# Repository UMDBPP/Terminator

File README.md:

# Terminator
A flight termination device for BPP.

## `T1100` - Current Revision

Much the same as T1000 but simpler and more complete.

## `T1000`
Shipman's ENEE499L project. The digital portion integrates a STM32L4, GPS, P/T Sensor, FRAM, and SX1262 Radio. This should provide quite a bit of flexibility in a small package while consuming minimal power. The digital board interfaces with a cutdown board which performs hot-wire termination like many other designs. However, this board is really just a barebones buck converter power stage that will be controlled by the digital board. This should provide increased flexiblity and efficiency over other implementations while also allowing T1000 to terminate even 550 paracord.

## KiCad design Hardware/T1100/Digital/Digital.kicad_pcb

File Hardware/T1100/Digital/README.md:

View in your browser: https://kicanvas.org/?repo=https%3A%2F%2Fgithub.com%2FUMDBPP%2FTerminator%2Ftree%2Fmain%2FHardware%2FT1100%2FDigital

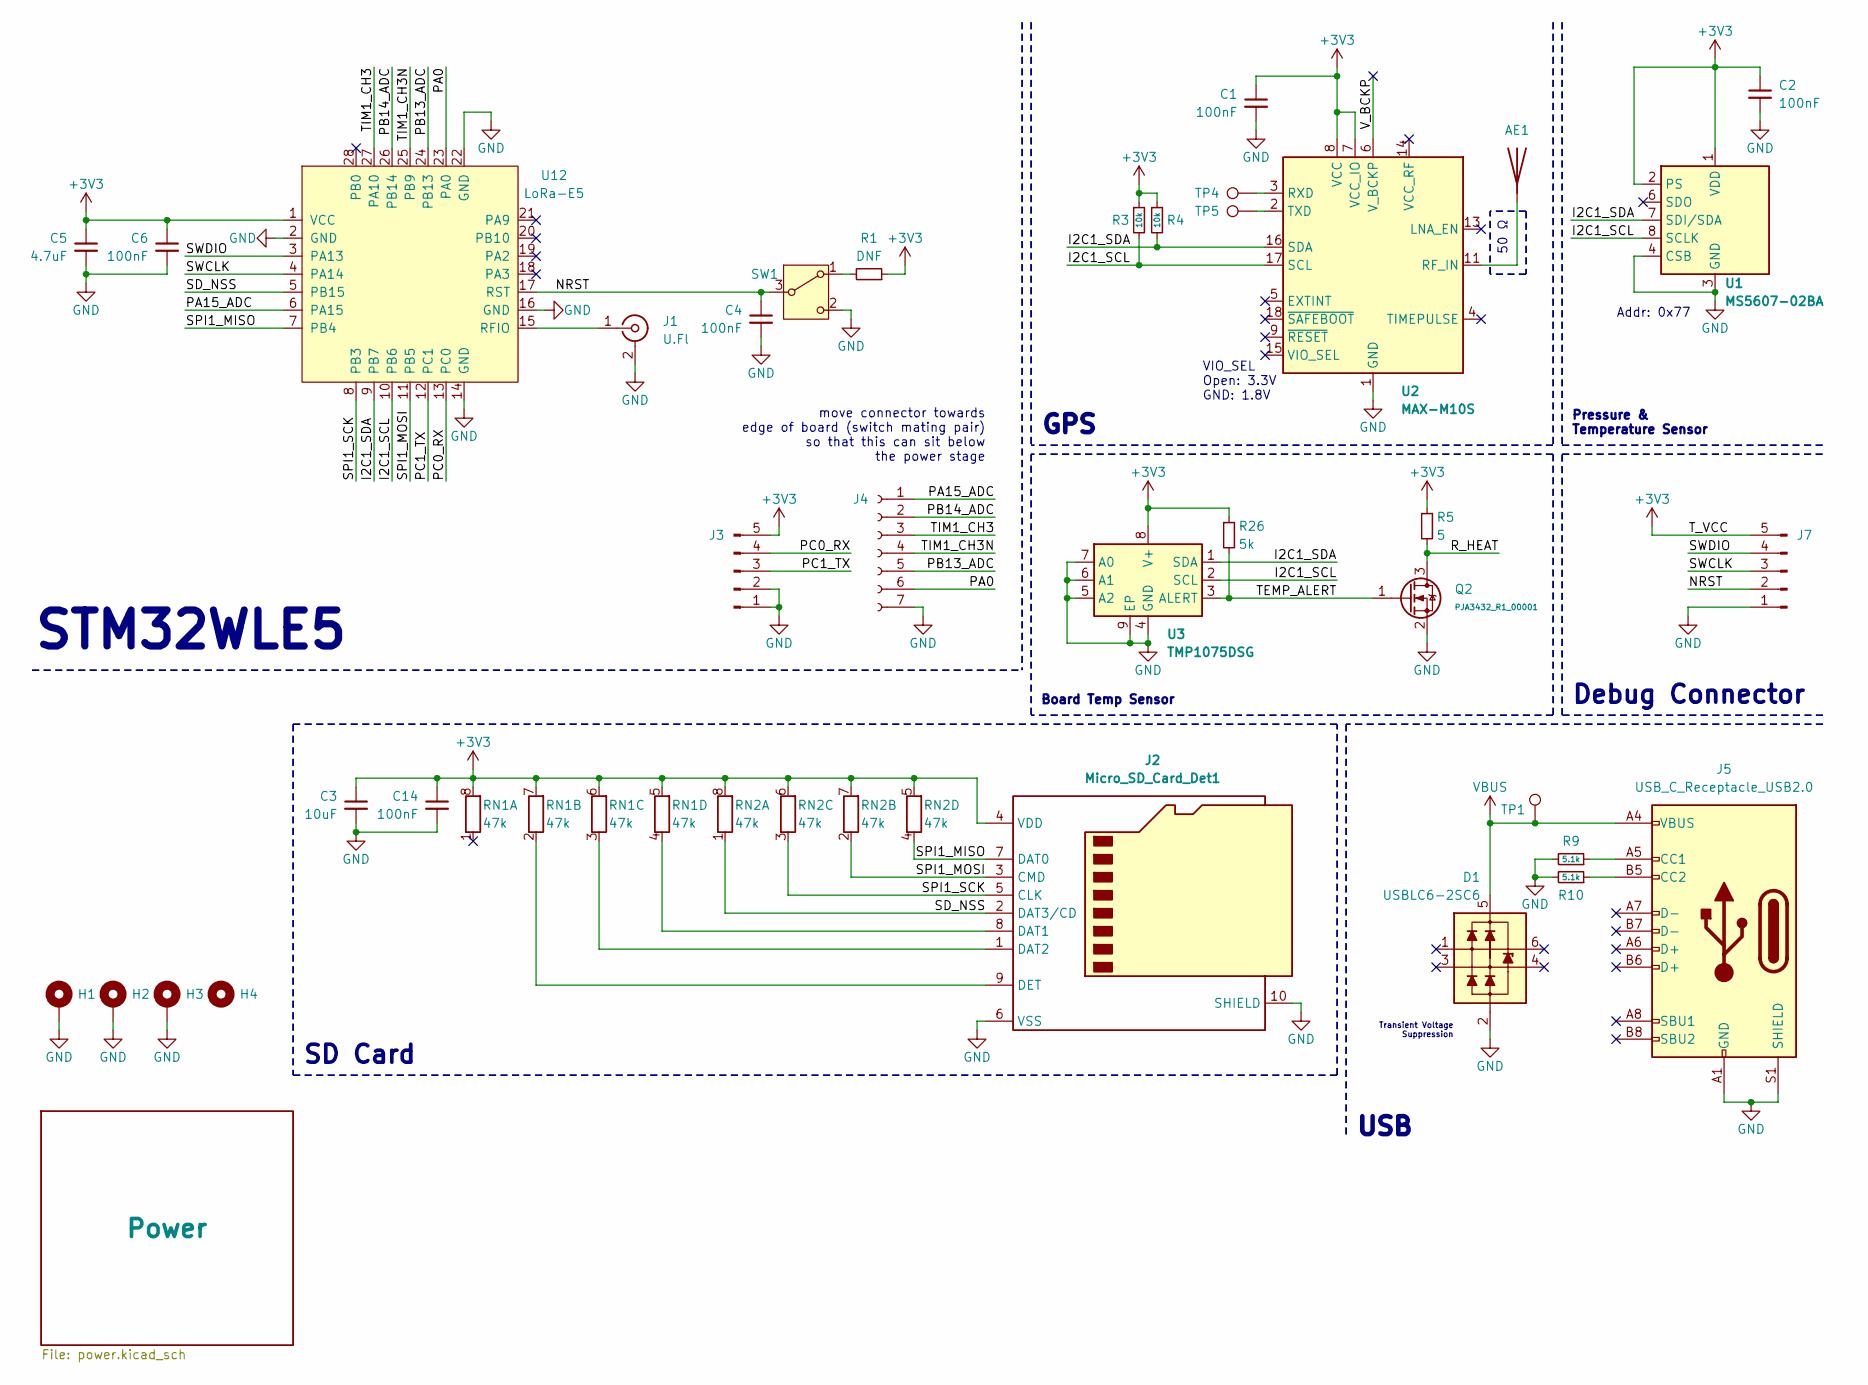
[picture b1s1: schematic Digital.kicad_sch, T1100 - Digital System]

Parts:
AE1: Antenna; ANT_1575AT_JOT-M
C1, C2, C4, C6, C14: 100nF; C_0402_1005Metric
C3: 10uF; C_0603_1608Metric
C5: 4.7uF; C_0603_1608Metric
D1: USBLC6-2SC6; TSOT-23-6
H1, H2, H3: MountingHole_Pad; Mounting_Wuerth_WA-SMSI-M2_H2mm_9774020243
H4: MountingHole; MountingHole_2.2mm_M2_DIN965
J1: U.Fl; U.FL_Molex_MCRF_73412-0110_Vertical
J2: Micro_SD_Card_Det1; microSD_HC_Molex_104031-0811
J3, J7: Conn_01x05_Pin; PinHeader_1x05_P2.54mm_Vertical
J4: Conn_01x07_Socket; Molex_ 1718570007
J5: USB_C_Receptacle_USB2.0; USB_C_Receptacle_GCT_USB4105-xx-A_16P_TopMnt_Horizontal
Q2: PJA3432_R1_00001; SOT-23
R1: DNF; R_0402_1005Metric
R3, R4: 10k; R_0402_1005Metric
R5: 5; R_0603_1608Metric
R9, R10: 5.1k; R_0402_1005Metric
R26: 5k; R_0402_1005Metric
RN1, RN2: 47k; R_Array_Convex_4x1206
SW1: SW_SPDT; CAS-120TB_NDC-M
TP1: TestPoint; TestPoint_Pad_D1.0mm
TP4, TP5: TestPoint; TestPoint_Pad_D3.0mm
U1: MS5607-02BA; LGA-8_3x5mm_P1.25mm
U2: MAX-M10S; ublox_MAX
U3: TMP1075DSG; WSON-8-1EP_2x2mm_P0.5mm_EP0.9x1.6mm_ThermalVias
U12: LoRa-E5

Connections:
+3V3: C1.1, C2.1, C3.1, C5.1, C6.1, C14.1, J2.4 (VDD), J3.5, J7.5, R1.1, R3.1, R4.1, R5.1, R26.1, RN1.5 (R4.2), RN1.6 (R3.2), RN1.7 (R2.2), RN1.8 (R1.2), RN2.5 (R4.2), RN2.6 (R3.2), RN2.7 (R2.2), RN2.8 (R1.2), U1.1 (VDD), U1.2 (PS), U2.7 (VCC_IO), U2.8 (VCC), U3.8 (V+), U12.1 (VCC); also elsewhere on the board
/I2C1_SCL: R3.2, U1.8 (SCLK), U2.17 (SCL), U3.2 (SCL), U12.10 (PB6)
/I2C1_SDA: R4.2, U1.7 (SDI/SDA), U2.16 (SDA), U3.1 (SDA), U12.9 (PB7)
/NRST: C4.1, J7.2, SW1.3 (C), U12.17 (RST)
/PA0: J4.6, U12.23 (PA0)
/PA15_ADC: J4.1, U12.6 (PA15)
/PB13_ADC: J4.5, U12.24 (PB13~)
/PB14_ADC: J4.2, U12.26 (PB14)
/PC0_RX: J3.4, U12.13 (PC0)
/PC1_TX: J3.3, U12.12 (PC1)
/R_HEAT: Q2.3 (D), R5.2
/SD_NSS: J2.2 (DAT3/CD), RN2.1 (R1.1), U12.5 (PB15)
/SPI1_MISO: J2.7 (DAT0), RN2.4 (R4.1), U12.7 (PB4)
/SPI1_MOSI: J2.3 (CMD), RN2.2 (R2.1), U12.11 (PB5)
/SPI1_SCK: J2.5 (CLK), RN2.3 (R3.1), U12.8 (PB3)
/SWCLK: J7.3, U12.4 (PA14)
/SWDIO: J7.4, U12.3 (PA13)
/TEMP_ALERT: Q2.1 (G), R26.2, U3.3 (ALERT)
/TIM1_CH3: J4.3, U12.27 (PA10)
/TIM1_CH3N: J4.4, U12.25 (PB9)
/V_BCKP: U2.6 (V_BCKP)
GND: C1.2, C2.2, C3.2, C4.2, C5.2, C6.2, C14.2, D1.2 (VN), H1.1, H2.1, H3.1, J1.2 (Ext), J2.6 (VSS), J2.10 (SHIELD), J3.1, J3.2, J4.7, J5.A1 (GND), J5.A12 (GND), J5.B1 (GND), J5.B12 (GND), J5.S1 (SHIELD), J7.1, Q2.2 (S), R9.2, R10.2, SW1.2 (B), U1.3 (GND), U1.4 (CSB), U1.5 (CSB), U2.1 (GND), U2.10 (GND), U2.12 (GND), U3.4 (GND), U3.5 (A2), U3.6 (A1), U3.7 (A0), U3.9 (EP), U12.2 (GND), U12.14 (GND), U12.16 (GND), U12.22 (GND); also elsewhere on the board
unnamed: AE1.1 (A), U2.11 (RF_IN)
unnamed: J1.1 (In), U12.15 (RFIO)
unnamed: J2.8 (DAT1), RN1.4 (R4.1)
unnamed: J2.1 (DAT2), RN1.3 (R3.1)
unnamed: J2.9 (DET), RN1.2 (R2.1)
unnamed: J5.A5 (CC1), R9.1
unnamed: J5.B5 (CC2), R10.1
unnamed: R1.2, SW1.1 (A)
unnamed: TP4.1, U2.3 (RXD)
unnamed: TP5.1, U2.2 (TXD)
VBUS: D1.5 (VP), J5.A4 (VBUS), J5.A9 (VBUS), J5.B4 (VBUS), J5.B9 (VBUS), TP1.1; also elsewhere on the board

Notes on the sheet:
GPS
Transient Voltage Suppression
Board Temp Sensor
VIO_SEL Open: 3.3V GND: 1.8V
Debug Connector
SD Card
50 Ω
USB
Pressure & Temperature Sensor
move connector towards edge of board (switch mating pair) so that this can sit below the power stage
STM32WLE5
Addr: 0x77

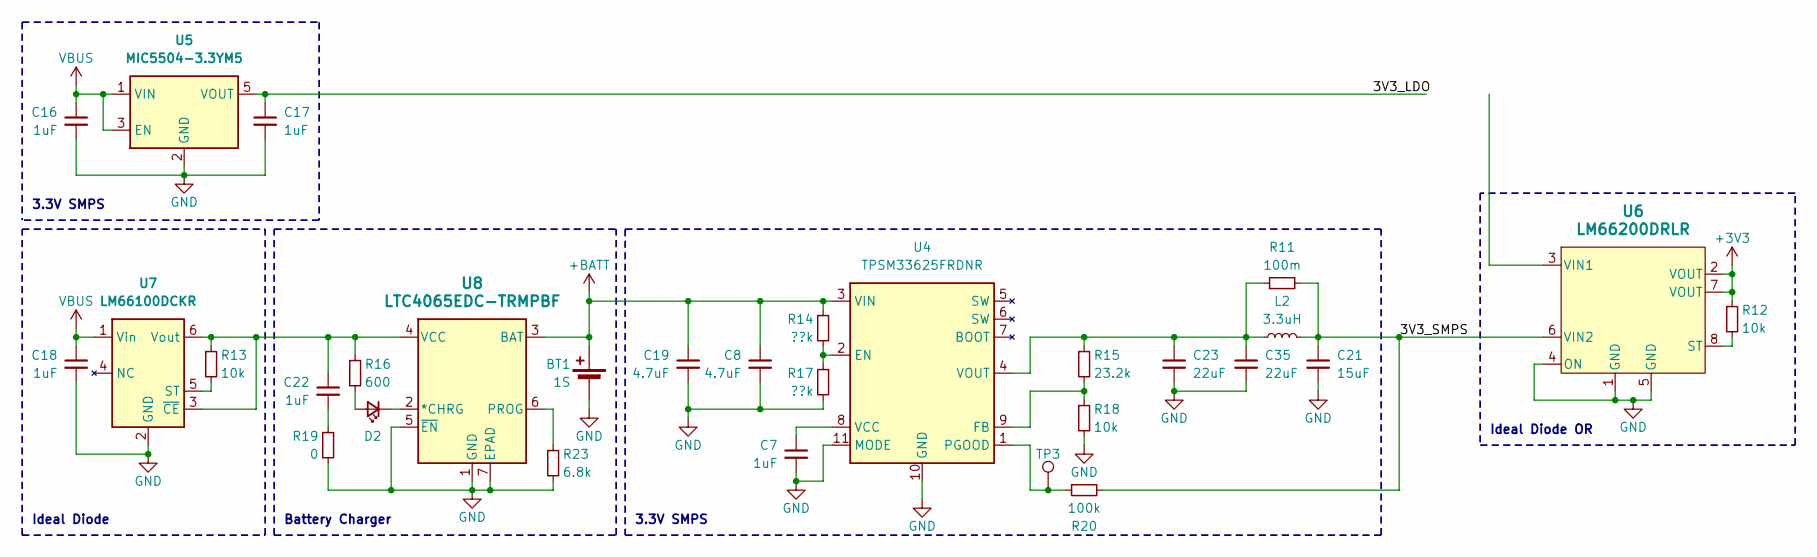
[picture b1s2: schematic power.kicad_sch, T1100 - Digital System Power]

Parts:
BT1: 1S; PinHeader_1x02_P2.54mm_Vertical
C7: 1uF; C_0402_1005Metric
C8, C19: 4.7uF; C_0805_2012Metric
C16, C17, C18, C22: 1uF; C_0603_1608Metric
C21: 15uF; C_1206_3216Metric
C23, C35: 22uF; C_0805_2012Metric
D2: LED_Small; LED_0603_1608Metric
L2: 3.3uH; L_1210_3225Metric
R11: 100m; R_0402_1005Metric
R12, R13, R18: 10k; R_0402_1005Metric
R14, R17: ??k; R_0402_1005Metric
R15: 23.2k; R_0402_1005Metric
R16: 600; R_0402_1005Metric
R19: 0; R_0402_1005Metric
R20: 100k; R_0402_1005Metric
R23: 6.8k; R_0402_1005Metric
TP3: TestPoint; TestPoint_Pad_D1.0mm
U4: TPSM33625FRDNR; RDN0011A-MFG-NO-VIA
U5: MIC5504-3.3YM5; SOT-23-5
U6: LM66200DRLR; SOT-5X3_DRL_TEX
U7: LM66100DCKR; SOT-363_SC-70-6
U8: LTC4065EDC-TRMPBF; DFN-6_DC_LIT

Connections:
+3V3: R12.1, U6.2 (VOUT), U6.7 (VOUT); also elsewhere on the board
+BATT: BT1.1 (+), C8.1, C19.1, R14.1, U4.3 (VIN), U8.3 (BAT)
/Power/3V3_LDO: C17.1, U5.5 (VOUT)
/Power/3V3_SMPS: C21.1, L2.2, R11.2, R20.2, U6.6 (VIN2)
GND: BT1.2 (-), C7.2, C8.2, C16.2, C17.2, C18.2, C19.2, C21.2, C23.2, C35.2, R17.2, R18.2, R19.2, R23.2, U4.10 (GND), U4.11 (MODE), U5.2 (GND), U6.1 (GND), U6.4 (ON), U6.5 (GND), U7.2 (GND), U8.1 (GND), U8.5 (~EN), U8.7 (EPAD); also elsewhere on the board
unnamed: C22.2, R19.1
unnamed: D2.2 (A), R16.2
unnamed: D2.1 (K), U8.2 (*CHRG)
unnamed: R14.2, R17.1, U4.2 (EN)
unnamed: R15.2, R18.1, U4.9 (FB)
unnamed: R20.1, TP3.1, U4.1 (PGOOD)
unnamed: C7.1, U4.8 (VCC)
unnamed: C23.1, C35.1, L2.1, R11.1, R15.1, U4.4 (VOUT)
unnamed: R12.2, U6.8 (ST)
unnamed: R13.2, U7.5 (ST)
unnamed: C22.1, R13.1, R16.1, U7.3 (~CE), U7.6 (Vout), U8.4 (VCC)
unnamed: R23.1, U8.6 (PROG)
VBUS: C16.1, C18.1, U5.1 (VIN), U5.3 (EN), U7.1 (Vin); also elsewhere on the board

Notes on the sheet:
Ideal Diode
Battery Charger
Ideal Diode OR
3.3V SMPS

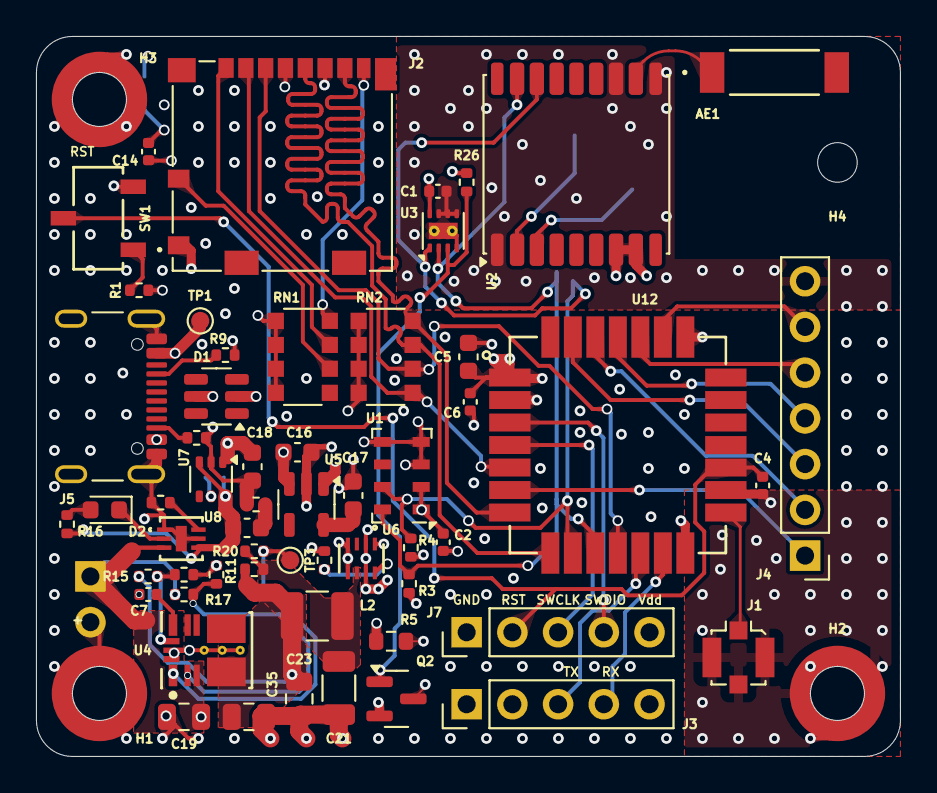
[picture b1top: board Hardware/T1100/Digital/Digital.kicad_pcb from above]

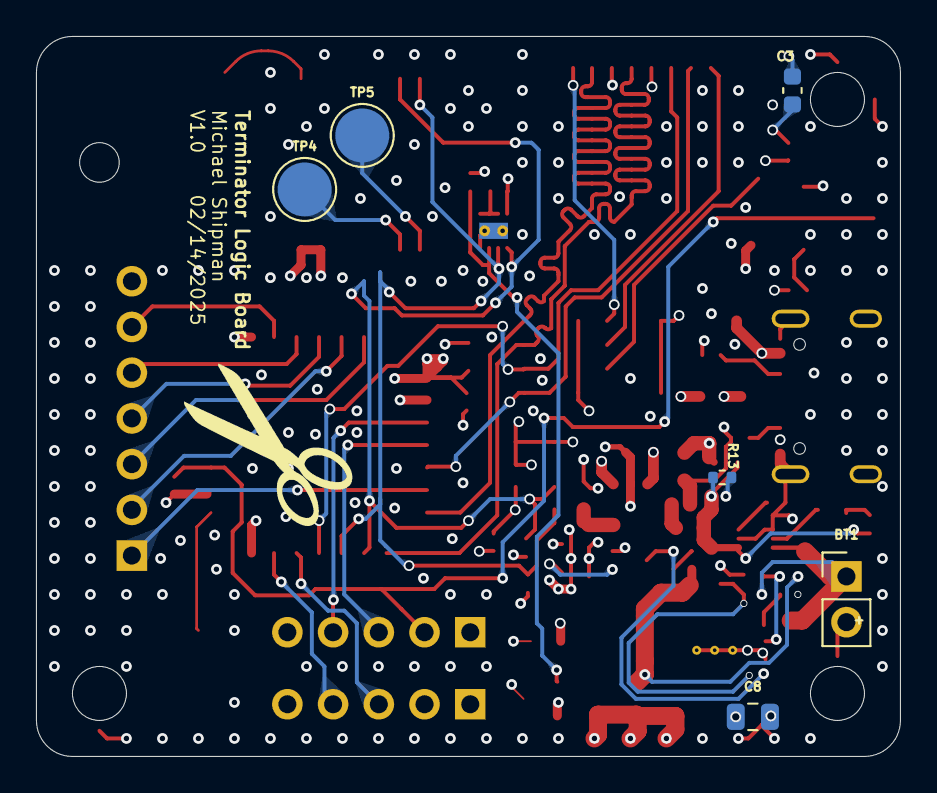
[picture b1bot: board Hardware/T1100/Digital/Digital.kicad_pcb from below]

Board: 6 copper layers, 48.0 x 40.0 mm, 67 parts (6 on the bottom side), 47 nets.

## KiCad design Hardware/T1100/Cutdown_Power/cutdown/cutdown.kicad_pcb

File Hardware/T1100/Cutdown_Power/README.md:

Cutdown power stage for T1000 nichrome. [Click here to view in browser.](https://kicanvas.org/?repo=https%3A%2F%2Fgithub.com%2FUMDBPP%2FTerminator%2Ftree%2Fmain%2FHardware%2FT1100%2FCutdown_Power%2Fcutdown)

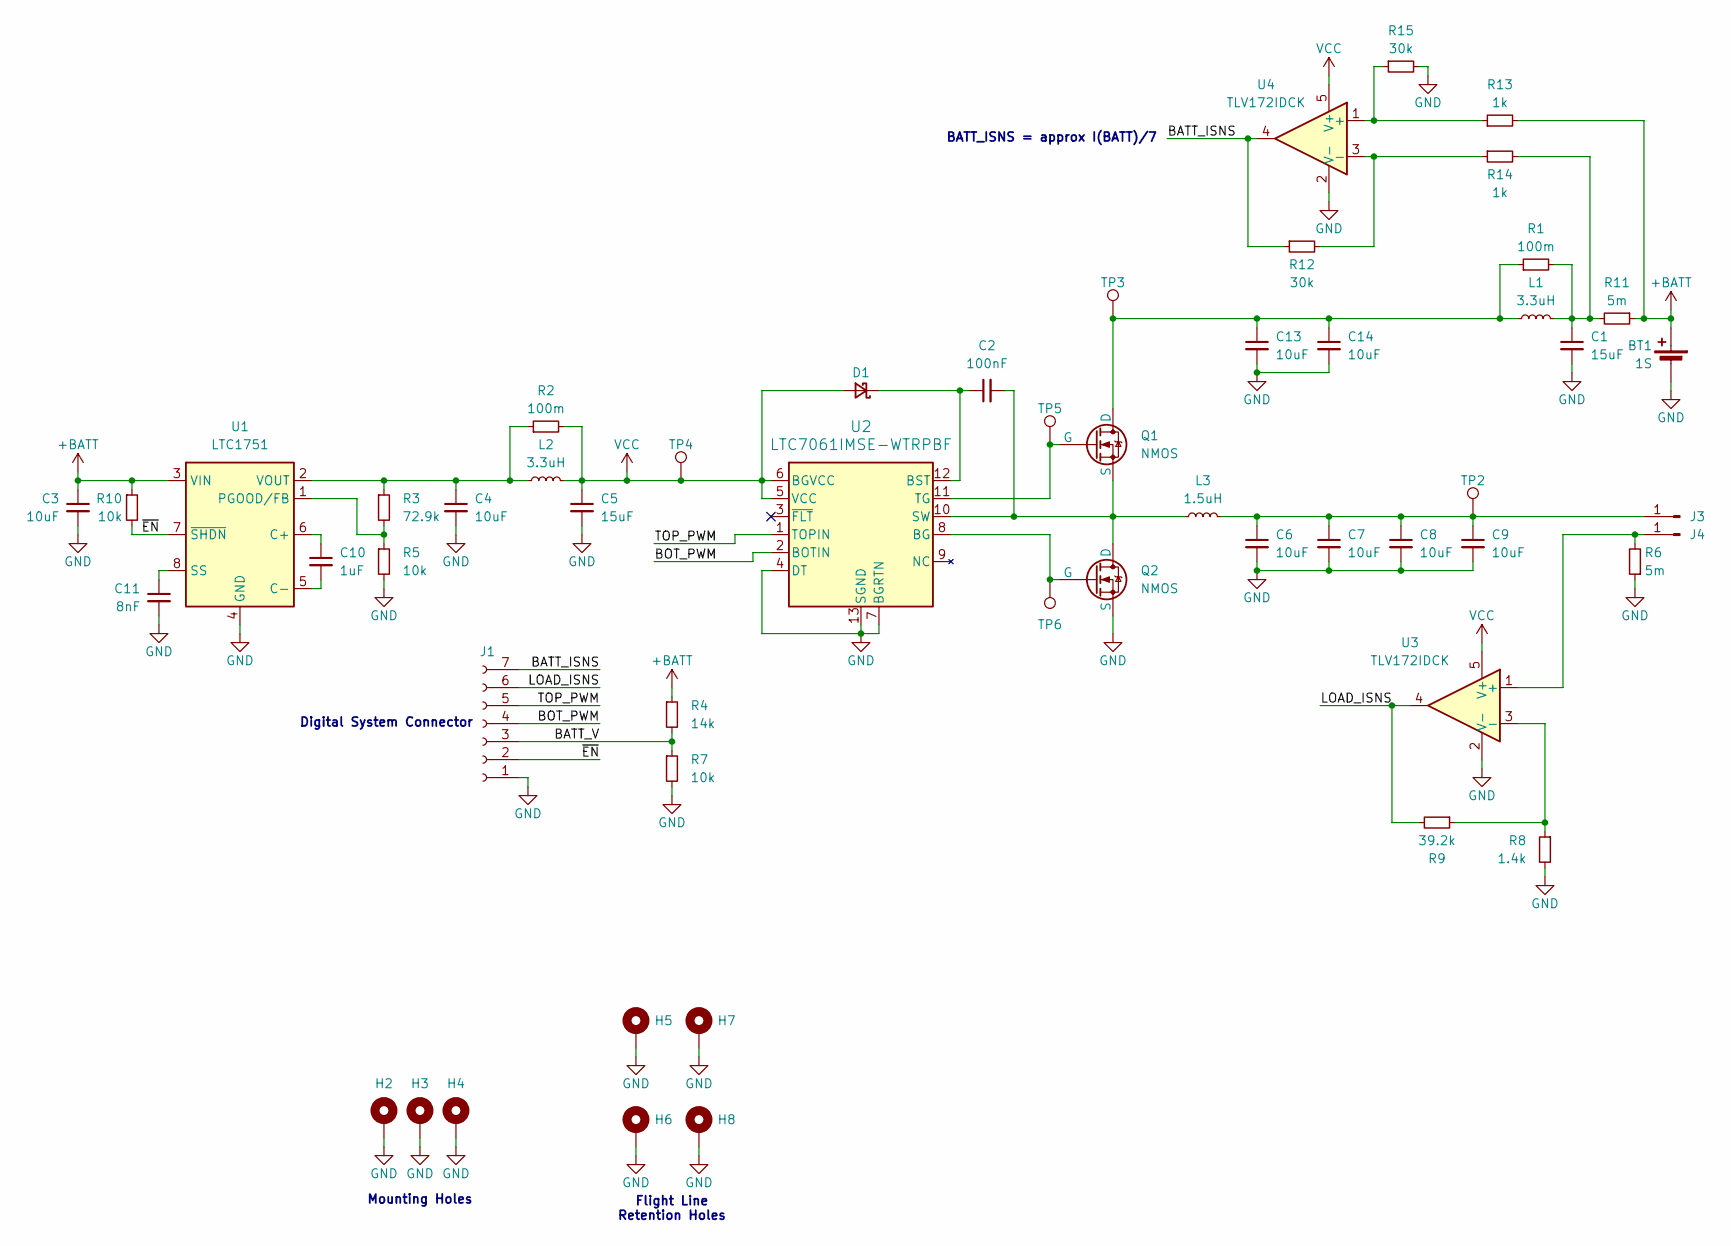
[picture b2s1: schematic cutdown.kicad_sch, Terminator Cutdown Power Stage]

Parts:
BT1: 1S; AMASS_XT30U-F_1x02_P5.0mm_Vertical
C1, C5: 15uF; C_1206_3216Metric
C2: 100nF; C_0603_1608Metric
C3, C4: 10uF; C_0805_2012Metric
C6, C7, C8, C9, C13, C14: 10uF; C_1206_3216Metric
C10: 1uF; C_0603_1608Metric
C11: 8nF; C_0603_1608Metric
D1: D_Schottky_Small; D_SOD-123F
H2, H3, H4: MountingHole_Pad; MountingHole_2.2mm_M2_DIN965_Pad
H5, H6, H7, H8: MountingHole_Pad; Mounting_Wuerth_WA-SMSI-M2_H2mm_9774020243
J1: Conn_01x07_Socket; Molex_ 1718570007
J3, J4: Conn_01x01_Pin; Mounting_Wuerth_WA-SMSI-M2_H2mm_9774020243
L1, L2: 3.3uH; L_1210_3225Metric
L3: 1.5uH; IHLP2020CZER1R5M8A
Q1, Q2: NMOS; CSD17307Q5A
R1, R2: 100m; C_0603_1608Metric
R3: 72.9k; R_0402_1005Metric
R4: 14k; R_0402_1005Metric
R5, R7, R10: 10k; R_0402_1005Metric
R6, R11: 5m; R_2512_6332Metric
R8: 1.4k; R_0603_1608Metric_Pad0.98x0.95mm_HandSolder
R9: 39.2k; R_0603_1608Metric_Pad0.98x0.95mm_HandSolder
R12, R15: 30k; R_0402_1005Metric
R13, R14: 1k; R_0402_1005Metric
TP2, TP3, TP4: TestPoint; TestPoint_Keystone_5000-5004_Miniature
TP5, TP6: TestPoint; TestPoint_Pad_D1.0mm
U1: LTC1751; MSOP-8_3x3mm_P0.65mm
U2: LTC7061IMSE-WTRPBF; MSOP-12-1EP_3x4mm_P0.65mm_EP1.65x2.85mm
U3, U4: TLV172IDCK; SOT-353_SC-70-5

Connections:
+BATT: BT1.2 (+), C3.1, R4.1, R10.1, R11.1, R13.2, U1.3 (VIN)
/BATT_ISNS: J1.7, R12.1, U4.4
/BATT_V: J1.3, R4.2, R7.1
/BOT_PWM: J1.4, U2.2 (BOTIN)
/LOAD_ISNS: J1.6, R9.2, U3.4
/TOP_PWM: J1.5, U2.1 (TOPIN)
/~EN: J1.2, R10.2, U1.7 (~SHDN)
GND: BT1.1 (-), C1.2, C3.2, C4.2, C5.2, C6.2, C7.2, C8.2, C9.2, C11.2, C13.2, C14.2, H2.1, H3.1, H4.1, H5.1, H6.1, H7.1, H8.1, J1.1, Q2.3 (S), R5.2, R6.1, R7.2, R8.2, R15.2, U1.4 (GND), U2.4 (DT), U2.7 (BGRTN), U2.13 (SGND), U3.2 (V-), U4.2 (V-)
unnamed: C1.1, L1.2, R1.2, R11.2, R14.2
unnamed: C2.1, D1.1 (K), U2.12 (BST)
unnamed: C6.1, C7.1, C8.1, C9.1, J3.1, L3.2, TP2.1
unnamed: J4.1, R6.2, U3.1 (+)
unnamed: C13.1, C14.1, L1.1, Q1.1 (D), R1.1, TP3.1
unnamed: Q1.2 (G), TP5.1, U2.11 (TG)
unnamed: C2.2, L3.1, Q1.3 (S), Q2.1 (D), U2.10 (SW)
unnamed: Q2.2 (G), TP6.1, U2.8 (BG)
unnamed: C10.1, U1.6 (C+)
unnamed: C10.2, U1.5 (C-)
unnamed: R3.2, R5.1, U1.1 (PGOOD/FB)
unnamed: C11.1, U1.8 (SS)
unnamed: C4.1, L2.1, R2.1, R3.1, U1.2 (VOUT)
unnamed: R8.1, R9.1, U3.3 (-)
unnamed: R13.1, R15.1, U4.1 (+)
unnamed: R12.2, R14.1, U4.3 (-)
VCC: C5.1, D1.2 (A), L2.2, R2.2, TP4.1, U2.5 (VCC), U2.6 (BGVCC), U3.5 (V+), U4.5 (V+)

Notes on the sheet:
Digital System Connector
BATT_ISNS = approx I(BATT)/7
Flight Line Retention Holes
Mounting Holes

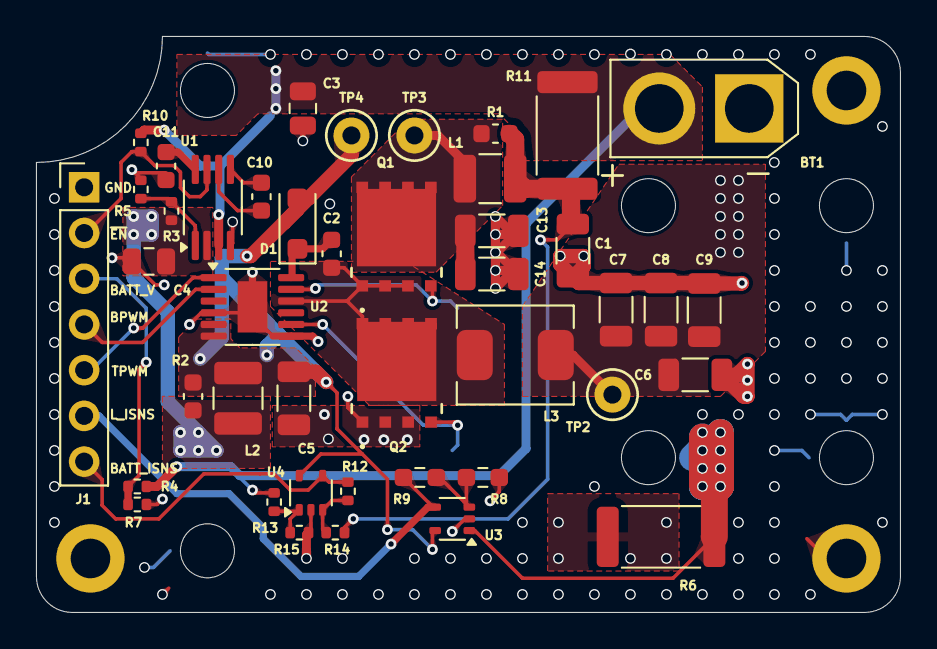
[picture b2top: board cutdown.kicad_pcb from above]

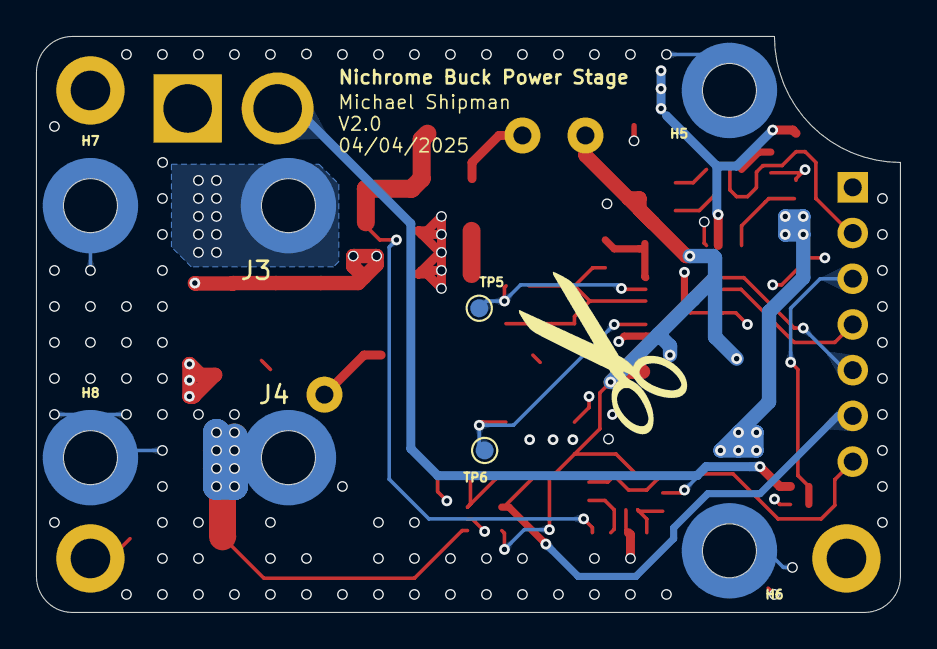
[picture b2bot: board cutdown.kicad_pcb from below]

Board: 4 copper layers, 48.0 x 32.0 mm, 54 parts (8 on the bottom side), 25 nets.

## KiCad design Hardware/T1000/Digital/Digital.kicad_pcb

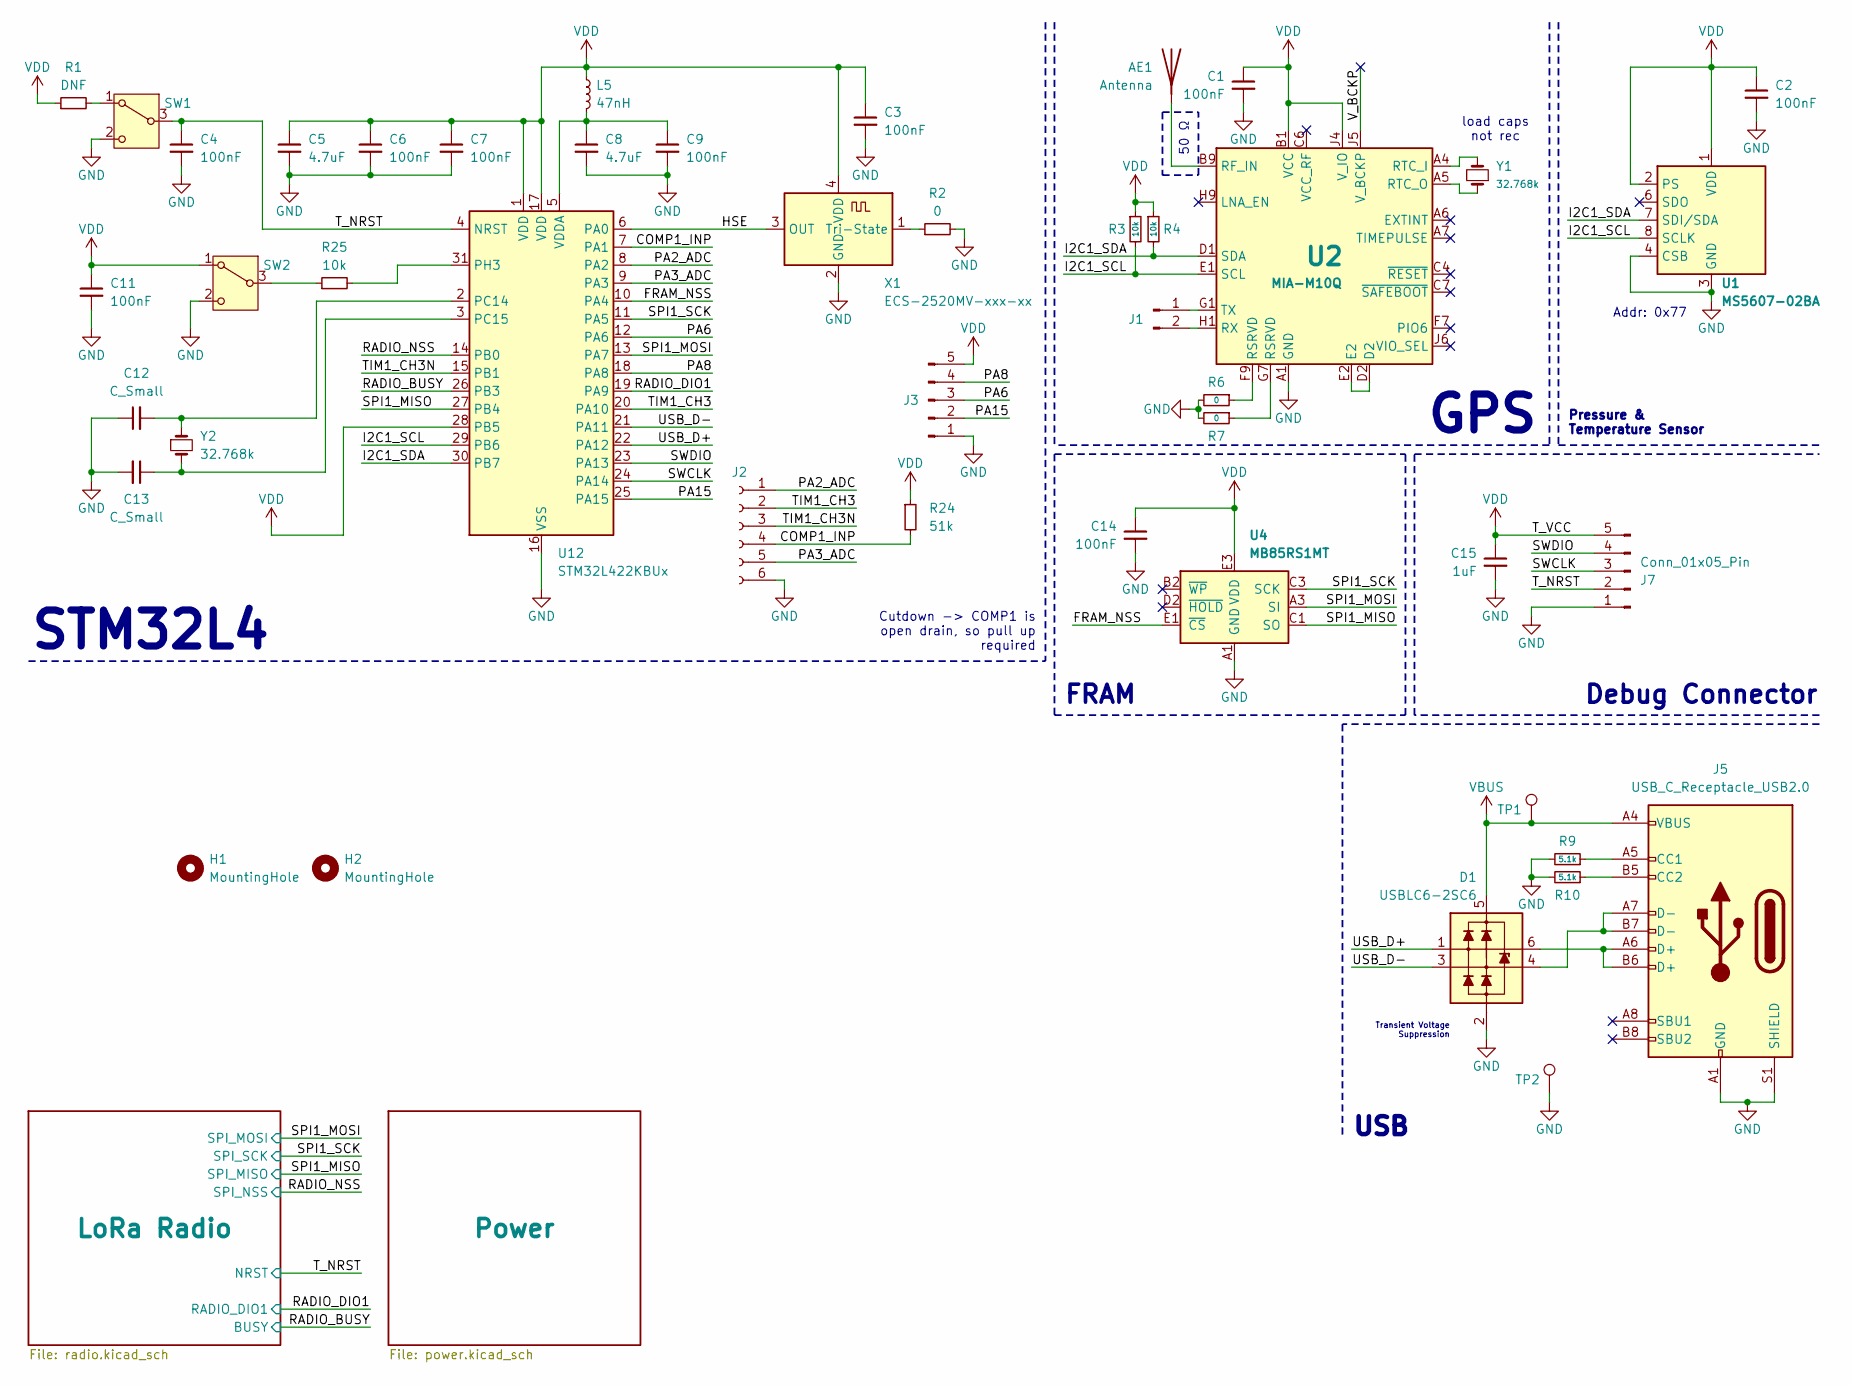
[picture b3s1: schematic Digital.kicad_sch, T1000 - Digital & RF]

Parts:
AE1: Antenna; ANT_1575AT_JOT-M
C1, C2, C3, C4, C6, C7, C9, C11, C14: 100nF; C_0402_1005Metric
C5, C8: 4.7uF; C_0603_1608Metric
C12, C13: C_Small; C_0402_1005Metric
C15: 1uF; C_0603_1608Metric
D1: USBLC6-2SC6; TSOT-23-6
H1, H2: MountingHole; MountingHole_2.2mm_M2
J1: Conn_01x02_Pin; PinHeader_1x02_P2.54mm_Vertical
J2: Conn_01x06_Socket; PinHeader_1x06_P2.54mm_Vertical
J3, J7: Conn_01x05_Pin; PinHeader_1x05_P2.54mm_Vertical
J5: USB_C_Receptacle_USB2.0; USB_C_Receptacle_GCT_USB4105-xx-A_16P_TopMnt_Horizontal
L5: 47nH; L_0402_1005Metric
R1: DNF; R_0402_1005Metric
R2, R6, R7: 0; R_0402_1005Metric
R3, R4, R25: 10k; R_0402_1005Metric
R9, R10: 5.1k; R_0402_1005Metric
R24: 51k; R_0402_1005Metric
SW1, SW2: SW_SPDT; CAS-120TB_NDC-M
TP1, TP2: TestPoint; TestPoint_Pad_D1.0mm
U1: MS5607-02BA; LGA-8_3x5mm_P1.25mm
U2: MIA-M10Q
U4: MB85RS1MT; BGA8CP30X40_5X3_309X228X35B25N
U12: STM32L422KBUx; QFN-32-1EP_5x5mm_P0.5mm_EP3.45x3.45mm
X1: ECS-2520MV-xxx-xx; Oscillator_SMD_ECS_2520MV-xxx-xx-4Pin_2.5x2.0mm
Y1, Y2: 32.768k; Crystal_SMD_3215-2Pin_3.2x1.5mm

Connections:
/COMP1_INP: J2.4, R24.2, U12.7 (PA1)
/FRAM_NSS: U4.E1 (~CS), U12.10 (PA4)
/HSE: U12.6 (PA0), X1.3 (OUT)
/I2C1_SCL: R3.2, U1.8 (SCLK), U2.E1 (SCL), U12.29 (PB6)
/I2C1_SDA: R4.2, U1.7 (SDI/SDA), U2.D1 (SDA), U12.30 (PB7)
/PA2_ADC: J2.1, U12.8 (PA2)
/PA3_ADC: J2.5, U12.9 (PA3)
/PA6: J3.3, U12.12 (PA6)
/PA8: J3.4, U12.18 (PA8)
/PA15: J3.2, U12.25 (PA15)
/RADIO_BUSY: U12.26 (PB3); also elsewhere on the board
/RADIO_DIO1: U12.19 (PA9); also elsewhere on the board
/RADIO_NSS: U12.14 (PB0); also elsewhere on the board
/SPI1_MISO: U4.C1 (SO), U12.27 (PB4); also elsewhere on the board
/SPI1_MOSI: U4.A3 (SI), U12.13 (PA7); also elsewhere on the board
/SPI1_SCK: U4.C3 (SCK), U12.11 (PA5); also elsewhere on the board
/SWCLK: J7.3, U12.24 (PA14)
/SWDIO: J7.4, U12.23 (PA13)
/TIM1_CH3: J2.2, U12.20 (PA10)
/TIM1_CH3N: J2.3, U12.15 (PB1)
/T_NRST: C4.1, J7.2, SW1.3 (C), U12.4 (NRST); also elsewhere on the board
/USB_D+: D1.1 (L1), U12.22 (PA12)
/USB_D-: D1.3 (L2), U12.21 (PA11)
/V_BCKP: U2.J5 (V_BCKP)
GND: C1.2, C2.2, C3.2, C4.2, C5.2, C6.2, C7.2, C8.2, C9.2, C11.2, C12.1, C13.2, C14.2, C15.2, D1.2 (VN), J2.6, J3.1, J5.A1 (GND), J5.A12 (GND), J5.B1 (GND), J5.B12 (GND), J5.S1 (SHIELD), J7.1, R2.2, R6.2, R7.2, R9.2, R10.2, SW1.2 (B), SW2.2 (B), TP2.1, U1.3 (GND), U1.4 (CSB), U1.5 (CSB), U2.A1 (GND), U2.A2 (GND), U2.A3 (GND), U2.A8 (GND), U2.A9 (GND), U2.B2 (GND), U2.B8 (GND), U2.C3 (GND), U2.C9 (GND), U2.E3 (GND), U2.E4 (GND), U2.E9 (GND), U2.F1 (GND), U2.F3 (GND), U2.F4 (GND), U2.G3 (GND), U2.G4 (GND), U2.G5 (GND), U2.G6 (GND), U2.H8 (GND), U2.J8 (GND), U2.J9 (GND), U4.A1 (GND), U12.16 (VSS), U12.32 (VSS), U12.33 (VSS), X1.2 (GND); also elsewhere on the board
unnamed: AE1.1 (A), U2.B9 (RF_IN)
unnamed: D1.6 (L1), J5.A6 (D+), J5.B6 (D+)
unnamed: D1.4 (L2), J5.A7 (D-), J5.B7 (D-)
unnamed: J1.1, U2.G1 (TX)
unnamed: J1.2, U2.H1 (RX)
unnamed: J5.A5 (CC1), R9.1
unnamed: J5.B5 (CC2), R10.1
unnamed: R6.1, U2.F9 (RSRVD)
unnamed: R7.1, U2.G7 (RSRVD)
unnamed: R1.2, SW1.1 (A)
unnamed: R25.1, SW2.3 (C)
unnamed: U2.A4 (RTC_I), Y1.2
unnamed: U2.A5 (RTC_O), Y1.1
unnamed: C12.2, U12.2 (PC14), Y2.1
unnamed: C13.1, U12.3 (PC15), Y2.2
unnamed: R25.2, U12.31 (PH3)
unnamed: C8.1, C9.1, L5.2, U12.5 (VDDA)
unnamed: R2.1, X1.1 (Tri-State)
VBUS: D1.5 (VP), J5.A4 (VBUS), J5.A9 (VBUS), J5.B4 (VBUS), J5.B9 (VBUS), TP1.1; also elsewhere on the board
VDD: C1.1, C2.1, C3.1, C5.1, C6.1, C7.1, C11.1, C14.1, C15.1, J3.5, J7.5, L5.1, R1.1, R3.1, R4.1, R24.1, SW2.1 (A), U1.1 (VDD), U1.2 (PS), U2.B1 (VCC), U2.J4 (V_IO), U4.E3 (VDD), U12.1 (VDD), U12.17 (VDD), U12.28 (PB5), X1.4 (VDD); also elsewhere on the board

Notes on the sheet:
load caps not rec
GPS
Transient Voltage Suppression
Debug Connector
Cutdown -> COMP1 is open drain, so pull up required
FRAM
50 Ω
USB
Pressure & Temperature Sensor
STM32L4
Addr: 0x77

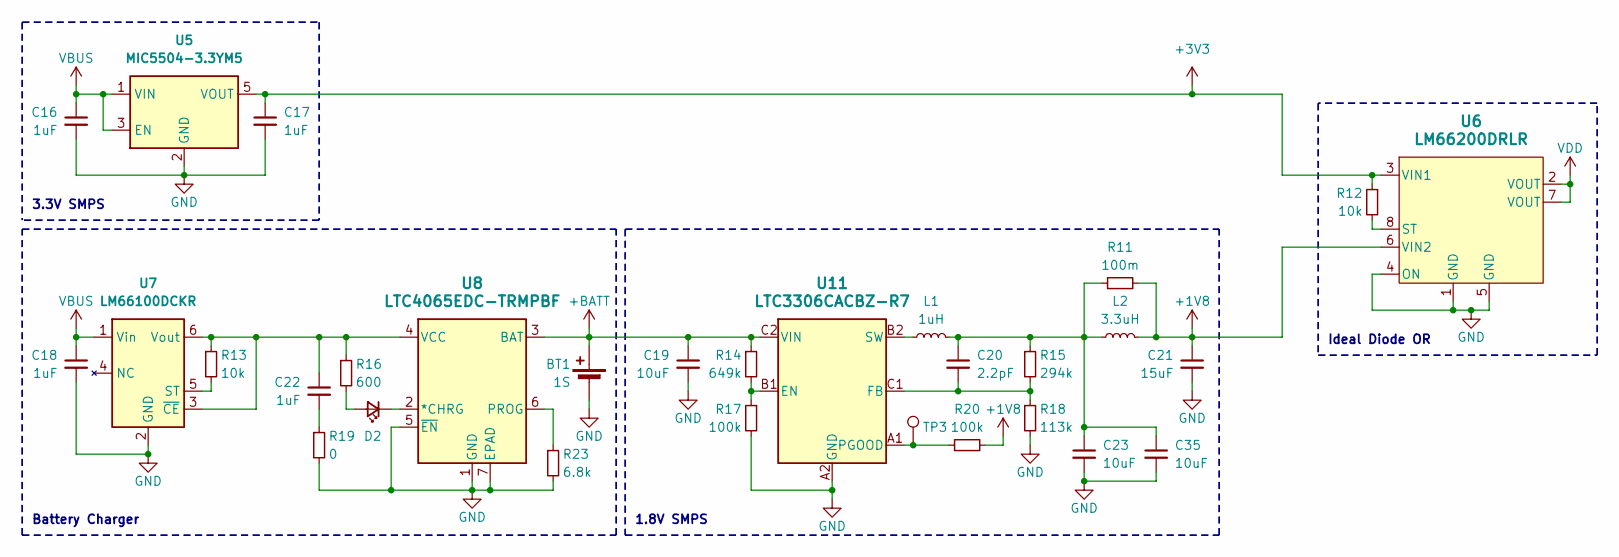
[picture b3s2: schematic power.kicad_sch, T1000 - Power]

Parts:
BT1: 1S; PinHeader_1x02_P2.54mm_Vertical
C16, C17, C18, C22: 1uF; C_0603_1608Metric
C19, C23, C35: 10uF; C_0805_2012Metric
C20: 2.2pF; C_0402_1005Metric
C21: 15uF; C_1206_3216Metric
D2: LED_Small; LED_0603_1608Metric
L1: 1uH; L_0805_2012Metric
L2: 3.3uH; L_1210_3225Metric
R11: 100m; R_0402_1005Metric
R12, R13: 10k; R_0402_1005Metric
R14: 649k; R_0402_1005Metric
R15: 294k; R_0402_1005Metric
R16: 600; R_0402_1005Metric
R17, R20: 100k; R_0402_1005Metric
R18: 113k; R_0402_1005Metric
R19: 0; R_0402_1005Metric
R23: 6.8k; R_0402_1005Metric
TP3: TestPoint; TestPoint_Pad_D1.0mm
U5: MIC5504-3.3YM5; SOT-23-5
U6: LM66200DRLR; SOT-5X3_DRL_TEX
U7: LM66100DCKR; SOT-363_SC-70-6
U8: LTC4065EDC-TRMPBF; DFN-6_DC_LIT
U11: LTC3306CACBZ-R7; CB-6-19_ADI

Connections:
+1V8: C21.1, L2.2, R11.2, R20.2, U6.6 (VIN2)
+3V3: C17.1, R12.1, U5.5 (VOUT), U6.3 (VIN1)
+BATT: BT1.1 (+), C19.1, R14.1, U8.3 (BAT), U11.C2 (VIN)
GND: BT1.2 (-), C16.2, C17.2, C18.2, C19.2, C21.2, C23.2, C35.2, R17.2, R18.2, R19.2, R23.2, U5.2 (GND), U6.1 (GND), U6.4 (ON), U6.5 (GND), U7.2 (GND), U8.1 (GND), U8.5 (~EN), U8.7 (EPAD), U11.A2 (GND); also elsewhere on the board
unnamed: C20.1, C23.1, C35.1, L1.2, L2.1, R11.1, R15.1
unnamed: C22.2, R19.1
unnamed: D2.2 (A), R16.2
unnamed: D2.1 (K), U8.2 (*CHRG)
unnamed: R12.2, U6.8 (ST)
unnamed: R13.2, U7.5 (ST)
unnamed: C22.1, R13.1, R16.1, U7.3 (~CE), U7.6 (Vout), U8.4 (VCC)
unnamed: R23.1, U8.6 (PROG)
unnamed: R14.2, R17.1, U11.B1 (EN)
unnamed: C20.2, R15.2, R18.1, U11.C1 (FB)
unnamed: R20.1, TP3.1, U11.A1 (PGOOD)
unnamed: L1.1, U11.B2 (SW)
VBUS: C16.1, C18.1, U5.1 (VIN), U5.3 (EN), U7.1 (Vin); also elsewhere on the board
VDD: U6.2 (VOUT), U6.7 (VOUT); also elsewhere on the board

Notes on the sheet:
Battery Charger
Ideal Diode OR
3.3V SMPS
1.8V SMPS
